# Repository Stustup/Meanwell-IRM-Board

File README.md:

# Meanwell IRM 20/30 Board

Simple board to quickly use the great Meanwell AC/DC power supply modules either in parallel or serien for a simple bipolar power supply. 

You can connect your project to the JST EH connectors or solder wires directly to the board. The footprint for the IRM Board is a combination of 
20W and 30W modules, so you can use both. For example, you could use two 48V PSUs for a 96V power supply to power low voltage tube amps, or use 
two IRM-20-15 in series with GND connected to the "Voltage Conenct" header to get a great, simple and cheap biplar power supply for headphone 
amps and such.

## Caution!

Always use an offboard switch and fuse in combination with these boards. There are many combined plug/switch/fuse boards like 
[these](https://www.mouser.de/ProductDetail/Qualtek/764-00-002?qs=uN5Dye%252BOwiXfVfVI0dfkHA%3D%3D) (there are always cheaper ones).

## TODO

- Place the AC connectors a little bit more intelligently. Now they almost touch the irm modules
- Place a shared 3 pin connector for directly accessing the bipolar psu
- power LEDs
- Power switch (maybe with relays and an optional bypass header)

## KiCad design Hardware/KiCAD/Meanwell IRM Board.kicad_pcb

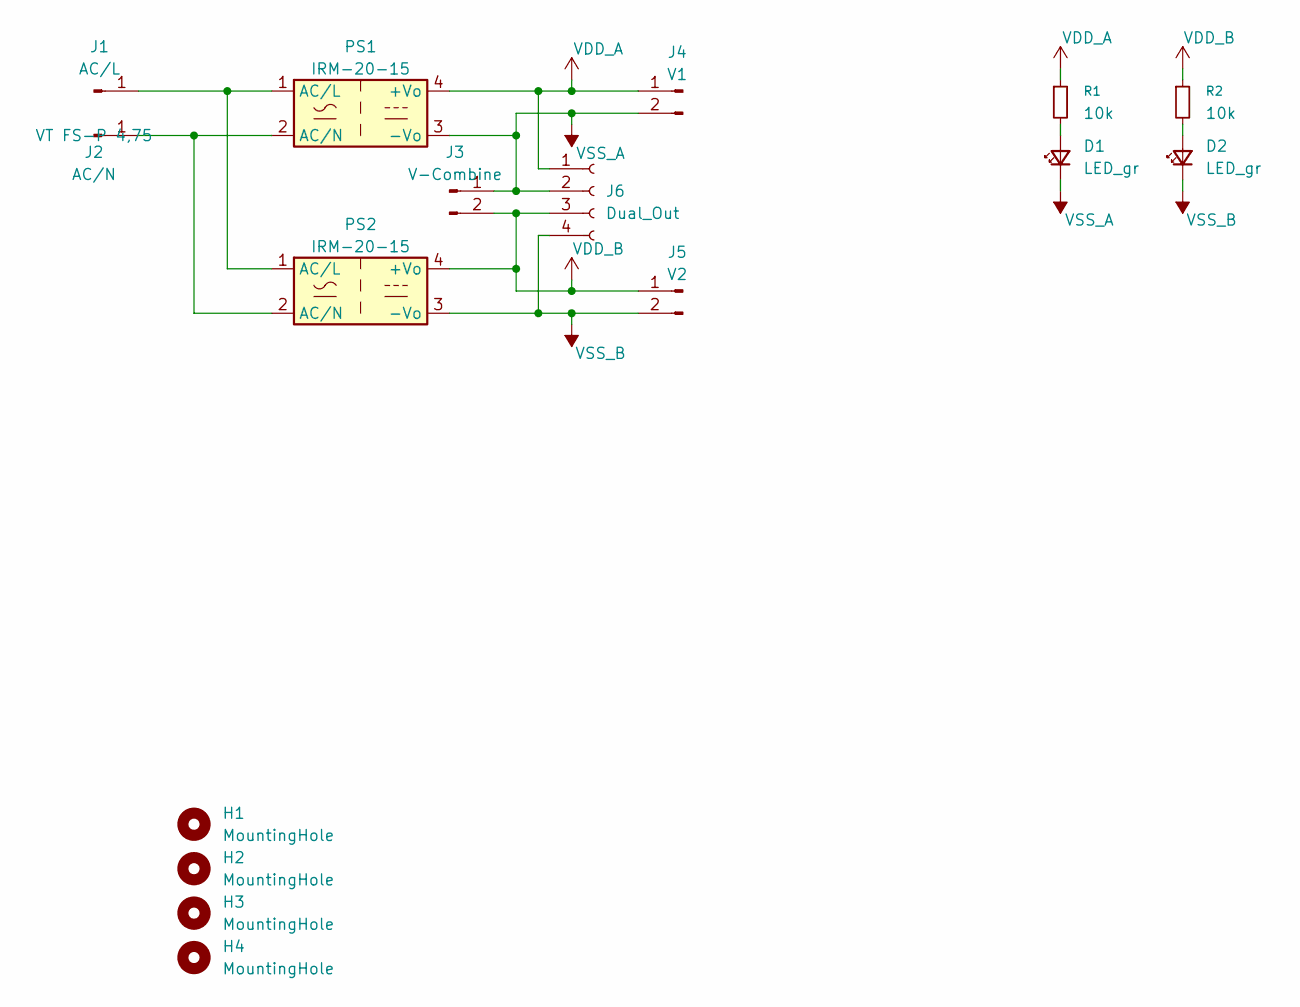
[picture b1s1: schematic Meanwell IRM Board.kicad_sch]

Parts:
D1, D2: LED_gr; LED_0805_2012Metric_Pad1.15x1.40mm_HandSolder
H1, H2, H3, H4: MountingHole; MountingHole_3.5mm
J1: AC/L; VT FS-P 4,75
J2: AC/N; VT FS-P 4,75
J3: V-Combine; PinHeader_1x02_P2.54mm_Vertical
J4: V1; JST_XH_B2B-XH-A_1x02_P2.50mm_Vertical
J5: V2; JST_XH_B2B-XH-A_1x02_P2.50mm_Vertical
J6: Dual_Out; JST_XH_B4B-XH-A_1x04_P2.50mm_Vertical
PS1, PS2: IRM-20-15; IRM Kombi; Mouser-Nr. 709-IRM20-15
R1, R2: 10k; R_0805_2012Metric_Pad1.20x1.40mm_HandSolder

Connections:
unnamed: D1.2 (A), R1.2
unnamed: D2.2 (A), R2.2
unnamed: J1.1, PS1.1 (AC/L), PS2.1 (AC/L)
unnamed: J2.1, PS1.2 (AC/N), PS2.2 (AC/N)
VDD_A: J4.1, J6.1, PS1.4 (+Vo), R1.1
VDD_B: J3.2, J5.1, J6.3, PS2.4 (+Vo), R2.1
VSS_A: D1.1 (K), J3.1, J4.2, J6.2, PS1.3 (-Vo)
VSS_B: D2.1 (K), J5.2, J6.4, PS2.3 (-Vo)

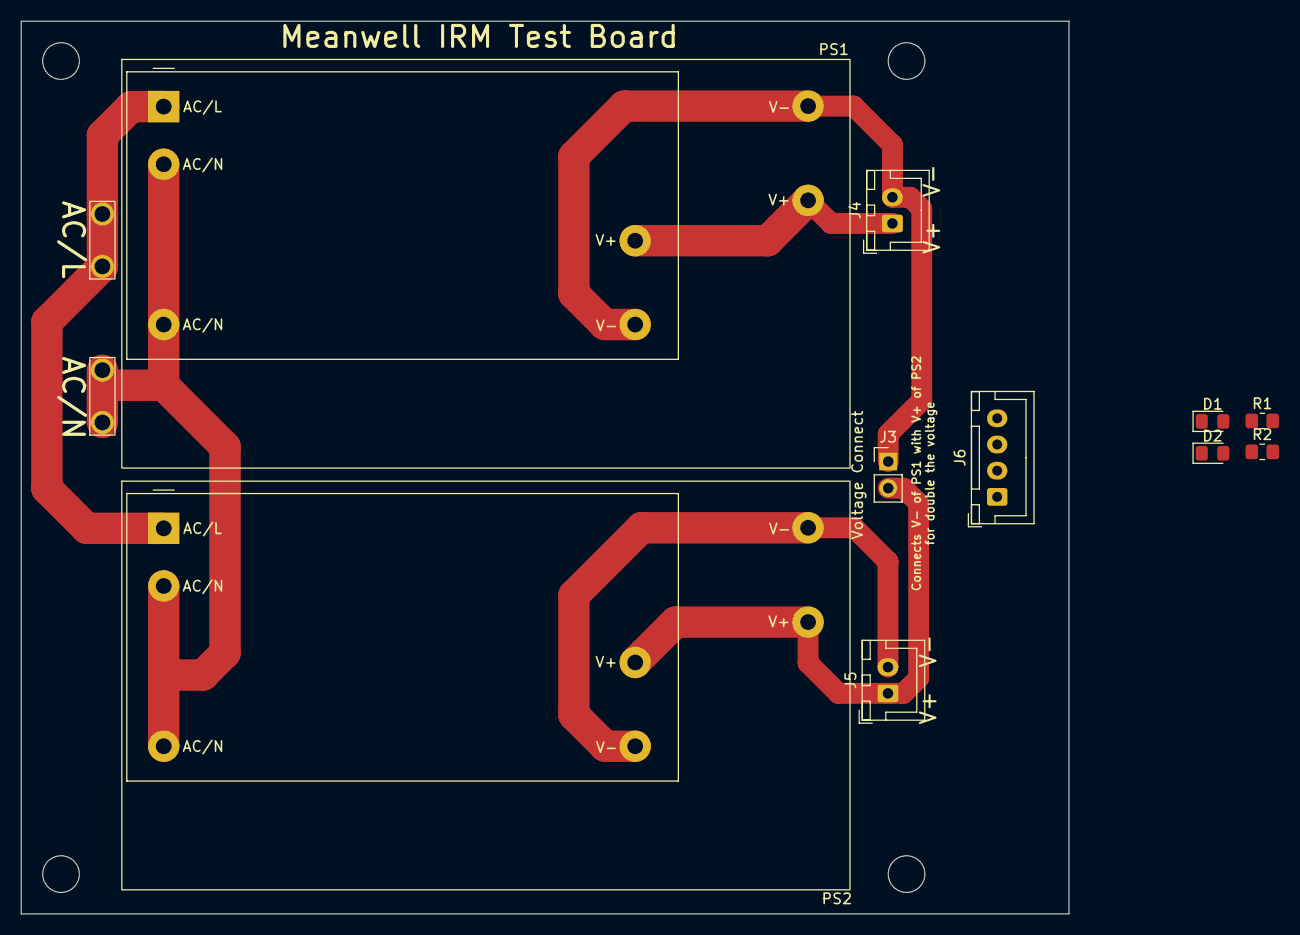
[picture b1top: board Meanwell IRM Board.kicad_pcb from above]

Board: 2 copper layers, 100.0 x 85.2 mm, 16 parts (0 on the bottom side), 8 nets.

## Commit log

2025-03-11 first commit + 3d models
2025-03-11 added readme and 3d view pictures
2025-03-11 added caution to readme
2025-03-11 spelling
2025-03-11 added reichelt nr for connectors
2025-03-19 Create LICENSE
2025-03-31 added TODOs
2025-03-31 started doing todos
